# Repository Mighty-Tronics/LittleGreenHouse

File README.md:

GNU General Public License v3 (GPLv3)
--------------------------------------------------------------------------------------------------------------------------
You are free to use, modify, and redistribute the code, as long as you keep the same license for your modified versions.

--------------------------------------------------------------------------------------------------------------------------

_LittleGreenHouse.ino the programm to upload in your arduino nano.

_Zip file include all librairies that must be installed in your Arduino IDE.

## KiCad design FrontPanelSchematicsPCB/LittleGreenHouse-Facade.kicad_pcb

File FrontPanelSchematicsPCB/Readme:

# Little Green House – Front Panel PCB (Facade)

This repository contains the KiCad files for the **Little Green House Facade PCB**, designed as the front control and interface panel for the Little Green House system. It includes interface elements such as OLED display, buttons, and status indicators, routed on a separate PCB to allow modularity and front-mounting.

## 📁 Files Overview

### 🖥️ Design Files (KiCad)
- `LittleGreenHouse-Facade.kicad_pcb`: PCB layout of the front panel
- `LittleGreenHouse-Facade.sch`: Schematic
- `LittleGreenHouse-Facade.pro`: Project settings
- `LittleGreenHouse-Facade-cache.lib`: Cached components
- `fp-info-cache`: Footprint cache (auto-generated)

### 🧾 Netlist & BOM
- `LittleGreenHouse-Facade.net`: Netlist file
- `LittleGreenHouse-Facade.xml`: XML export for online BOM tools

### 📐 Mechanical & Fabrication Files
- `LittleGreenHouse-Facade-B_Cu.dxf`, `.svg`, `.pdf`: Bottom copper layer
- `LittleGreenHouse-Facade-Edge_Cuts.dxf`, `.svg`, `.pdf`: Edge cut layer
- `LittleGreenHouse-Facade-F_SilkS.pdf`: Front silkscreen layer

### 🗃️ Backups
- `*.bak`, `*.sch-bak`: Automatic KiCad backups of schematic and PCB

## 🔧 How to Use

1. Open in **KiCad** (v6 or later).
2. Review or modify schematic and PCB.
3. Export files for CNC, milling, or manufacturing.
4. Integrate with the main **Little Green House** controller PCB.

## 📜 License

This design is published under the **CERN-OHL-S v2** license. It is freely reusable and modifiable under open hardware terms. See `LICENSE` for details.

## 🌱 About

Part of the [Little Green House Project](https://github.com/...), this front panel board is developed by **Mighty Tronics** as an open hardware interface for educational and hobbyist indoor plant automation.

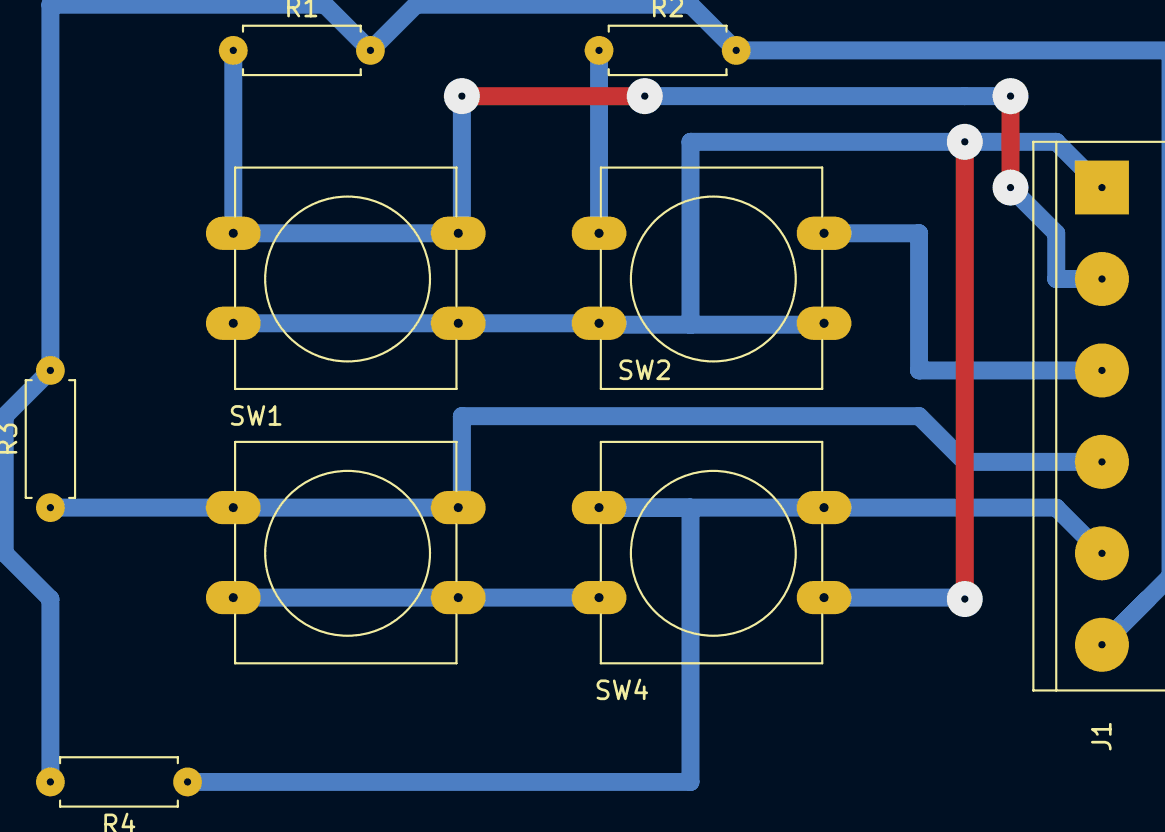
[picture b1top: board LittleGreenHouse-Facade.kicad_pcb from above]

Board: 2 copper layers, 9 parts (0 on the bottom side), 6 nets.

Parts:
J1: Conn_01x06_Male; TerminalBlock_bornier-6_P5.08mm
R1, R2, R3, R4: 10K; R_Axial_DIN0207_L6.3mm_D2.5mm_P7.62mm_Horizontal
SW1: Green; SW_PUSH-12mm
SW2: RED; SW_PUSH-12mm
SW3: YELLOW; SW_PUSH-12mm
SW4: BLUE; SW_PUSH-12mm

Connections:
+5V: J1.1, SW1.2, SW2.2, SW3.2, SW4.2
BLUE: J1.5, R4.1, SW4.1
GND: J1.6, R1.2, R2.2, R3.2, R4.2
GREEN: J1.2, R1.1, SW1.1
RED: J1.3, R2.1, SW2.1
YELLOW: J1.4, R3.1, SW3.1

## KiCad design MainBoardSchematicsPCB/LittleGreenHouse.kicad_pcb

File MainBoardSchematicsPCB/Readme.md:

# Little Green House – Open Hardware PCB Project

This repository contains the complete KiCad project files for the **Little Green House (LG)**, an open-source smart greenhouse controller. This PCB is designed to control and automate indoor plant care with features such as real-time clock, peristaltic pump, environmental sensors, and a user interface (OLED + buttons).

## 📁 Files Overview

### 🖥️ Design Files (KiCad)
- `LittleGreenHouse.kicad_pcb`: Main PCB layout
- `LittleGreenHouse.sch`: Main schematic
- `LittleGreenHouse.pro`: Project settings
- `LittleGreenHouse-cache.lib`, `LittleGreenHouse-cache.dcm`: Cached libraries
- `LittleGreenHouse-rescue.lib`, `LittleGreenHouse-rescue.dcm`: Rescued components
- `sym-lib-table`: Symbol library table

### 🧾 BOM & Netlist
- `LittleGreenHouse.csv`: Bill of Materials (BOM)
- `LittleGreenHouse.net`: Netlist
- `LittleGreenHouse.xml`: XML export for online BOM tools

### 📐 Mechanical & Fabrication Files
- `LittleGreenHouse-B_Cu.dxf`, `.svg`, `.pdf`: Bottom copper layer
- `LittleGreenHouse-F_SilkS.pdf`: Front silkscreen layer
- `LittleGreenHouse-Edge_Cuts.dxf`, `.svg`: Edge cuts for fabrication
- `LittleGreenHouseCarbide.c2d`: Carbide Create file for CNC routing

### 📄 Documentation
- `LittleGreenHouse.pdf`: Full schematic and layout export
- `LittleGreenHouse_SVG.svg`: Combined PCB graphic

### 🗃️ Backups
- `*.bak` and `*.bck` files: Automatic KiCad backups of schematic and PCB files

## 🔧 How to Use

1. Open the project in **KiCad** (version 6 or later recommended).
2. Modify or review the schematic and PCB as needed.
3. Export Gerbers or use the included files for manufacturing.
4. Refer to the [main documentation repository](https://github.com/...) for firmware and assembly instructions.

## 📜 License

This hardware is licensed under the **CERN-OHL-S v2** (or other you prefer). You are free to use, modify, and manufacture it under open hardware principles. Please refer to the `LICENSE` file for details.

## 🌱 About

This board is part of the [Little Green House project](https://github.com/...), an open-source smart greenhouse developed by **Mighty Tronics**.

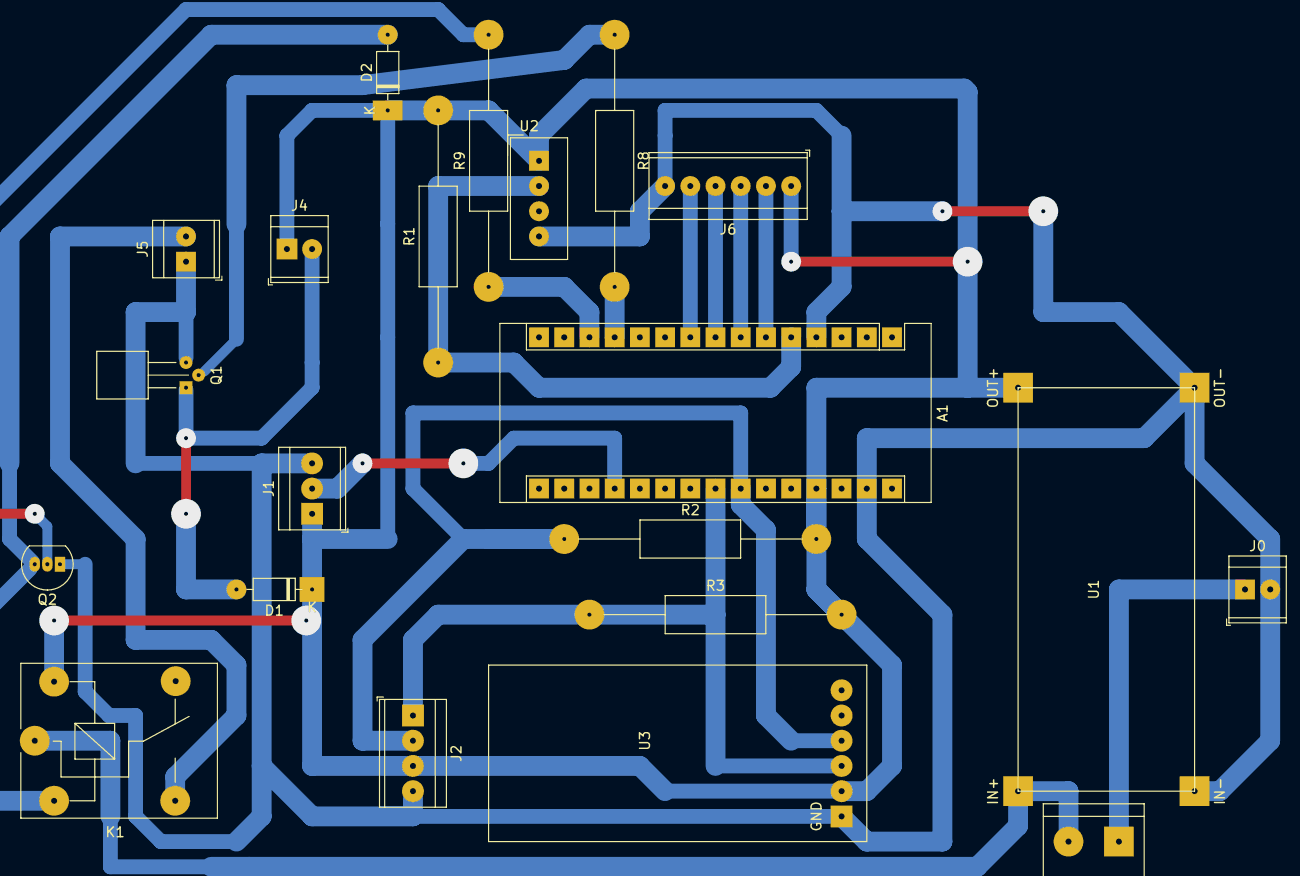
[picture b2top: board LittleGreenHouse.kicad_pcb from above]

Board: 2 copper layers, 21 parts (0 on the bottom side), 19 nets.

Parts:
A1: Arduino_Nano_Elegoo; Arduino_Nano
D1, D2: 1N4148; D_DO-35_SOD27_P7.62mm_Horizontal
J0: Power_Conn; TerminalBlock_TE_282834-2_1x02_P2.54mm_Horizontal
J1: Soil_Conn; TerminalBlock_TE_282834-3_1x03_P2.54mm_Horizontal
J2: Oled_Conn; TerminalBlock_TE_282834-4_1x04_P2.54mm_Horizontal
J4: PUMP_Conn; TerminalBlock_TE_282834-2_1x02_P2.54mm_Horizontal
J5: LedRamp_Conn; TerminalBlock_TE_282834-2_1x02_P2.54mm_Horizontal
J6: BP_Conn; TerminalBlock_TE_282834-6_1x06_P2.54mm_Horizontal
K1: SANYOU_SRD_Form_C; Relay_SPDT_SANYOU_SRD_Series_Form_C
Q1: BC337; TO-92_Horizontal2
Q2: 2N2222A; TO-92_Inline
R1, R9: 1K; R_Axial_DIN0411_L9.9mm_D3.6mm_P25.40mm_Horizontal
R2, R3: 10K; R_Axial_DIN0411_L9.9mm_D3.6mm_P25.40mm_Horizontal
R8: 330R; R_Axial_DIN0411_L9.9mm_D3.6mm_P25.40mm_Horizontal
SW1: SW_Power; TerminalBlock_bornier-2_P5.08mm
U1: 24V to 5V; Conv24DCtoDC
U2: DHT11; Aosong_DHT11_5.5x12.0_P2.54mm
U3: DS3231; DS3231_Mike

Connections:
+5V: A1.27, D1.1, D2.1, J1.1, J2.3, J4.1, J6.1, K1.5, R1.2, R2.2, R3.2, U1.3, U2.1, U3.2
+24V: K1.1, SW1.2, U1.1
BLUE: A1.9, J6.5
DC(+24V): J0.1, SW1.1
GND: A1.4, A1.29, J0.2, J1.3, J2.4, J5.1, J6.6, Q1.3, Q2.1, U1.2, U1.4, U2.4, U3.1
GREEN: A1.6, J6.2
LIGHT1: A1.13, R9.1
unnamed: A1.5, R1.1, U2.2
unnamed: A1.19, J1.2
unnamed: D1.2, J4.2, Q1.1
unnamed: D2.2, K1.2, Q2.3
unnamed: J5.2, K1.3
unnamed: Q1.2, R8.1
unnamed: Q2.2, R9.2
PUMP1: A1.12, R8.2
RED: A1.7, J6.3
SCL: A1.24, J2.2, R2.1, U3.4
SDA: A1.23, J2.1, R3.1, U3.3
YELLOW: A1.8, J6.4

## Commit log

2025-06-18 Add files via upload
    Librairies used by Little Green House code source.
2025-06-24 Create test
2025-06-24 Rename test to Readme
2025-06-24 Rename Lib4LittleGreenHouse.zip to SourceCode/Lib4LittleGreenHouse.zip
